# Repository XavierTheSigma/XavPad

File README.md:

# XavPad
XavPad is a 4x3 key macropad which uses KMK. I made this to help me be more productive.

## Features:
- 12 keys
- Simple case
- Dual layers 

## CAD Model:
The entire case fits together with 4 M3 screws.
The case has 2 seperate pieces: The Bottom and Sides, and the Top.

## PCB:
I made my PCB in KiCad

Schematic

PCB

## Firmware:
My hackpad uses [KMK](https://github.com/KMKfw/kmk_firmware) firmware.

- Swap between the 2 layers by double pressing the bottom left key
- The first layer are number pad 0-9
- The second layer are F1-12

For now it uses KMK but later on I might switch to QMK and add VIA support.

## BOM:
- 12x Cherry MX Switches
- 12x DSA Keycaps 
- 4x M3x16mm screws
- 12x through-hole 1N4148 Diodes
- 1x XIAO RP2040
- 1x Case (2 pieces)

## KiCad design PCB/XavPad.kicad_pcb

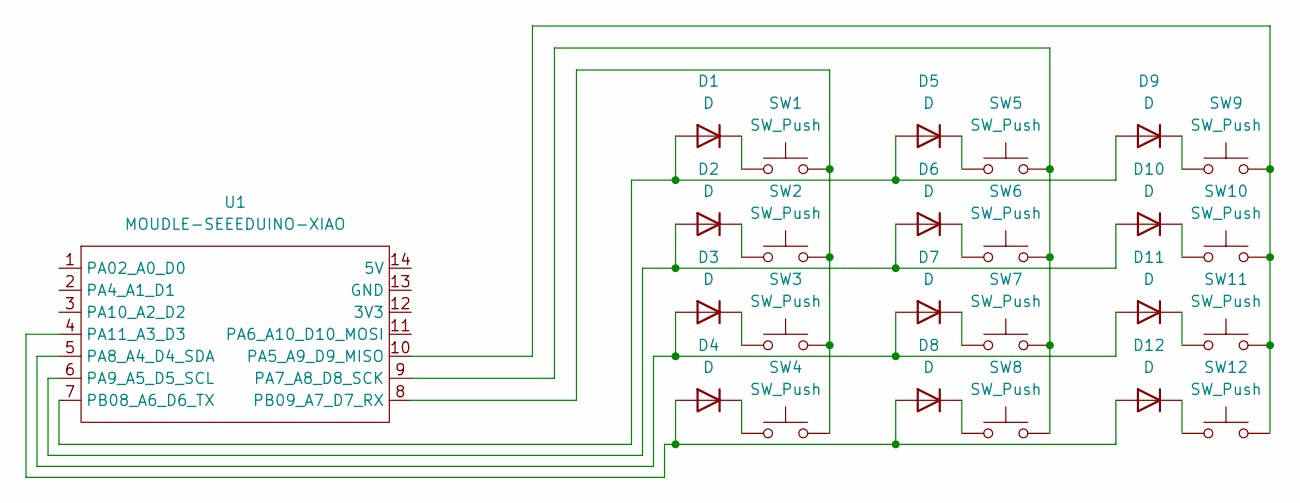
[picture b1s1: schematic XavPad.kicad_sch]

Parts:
D1, D2, D3, D4, D5, D6, D7, D8, D9, D10, D11, D12: D; D_DO-35_SOD27_P7.62mm_Horizontal
SW1, SW2, SW3, SW4, SW5, SW6, SW7, SW8, SW9, SW10, SW11, SW12: SW_Push; SW_Cherry_MX_1.00u_PCB
U1: MOUDLE-SEEEDUINO-XIAO; XIAO-Generic-Hybrid-14P-2.54-21X17.8MM

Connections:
unnamed: D1.2 (A), D5.2 (A), D9.2 (A), U1.7 (PB08_A6_D6_TX)
unnamed: D1.1 (K), SW1.1
unnamed: D2.1 (K), SW2.1
unnamed: D3.1 (K), SW3.1
unnamed: D4.1 (K), SW4.1
unnamed: D5.1 (K), SW5.1
unnamed: D6.1 (K), SW6.1
unnamed: D7.1 (K), SW7.1
unnamed: D8.1 (K), SW8.1
unnamed: D9.1 (K), SW9.1
unnamed: D2.2 (A), D6.2 (A), D10.2 (A), U1.6 (PA9_A5_D5_SCL)
unnamed: D10.1 (K), SW10.1
unnamed: D3.2 (A), D7.2 (A), D11.2 (A), U1.5 (PA8_A4_D4_SDA)
unnamed: D11.1 (K), SW11.1
unnamed: D4.2 (A), D8.2 (A), D12.2 (A), U1.4 (PA11_A3_D3)
unnamed: D12.1 (K), SW12.1
unnamed: SW9.2, SW10.2, SW11.2, SW12.2, U1.10 (PA5_A9_D9_MISO)
unnamed: SW5.2, SW6.2, SW7.2, SW8.2, U1.9 (PA7_A8_D8_SCK)
unnamed: SW1.2, SW2.2, SW3.2, SW4.2, U1.8 (PB09_A7_D7_RX)

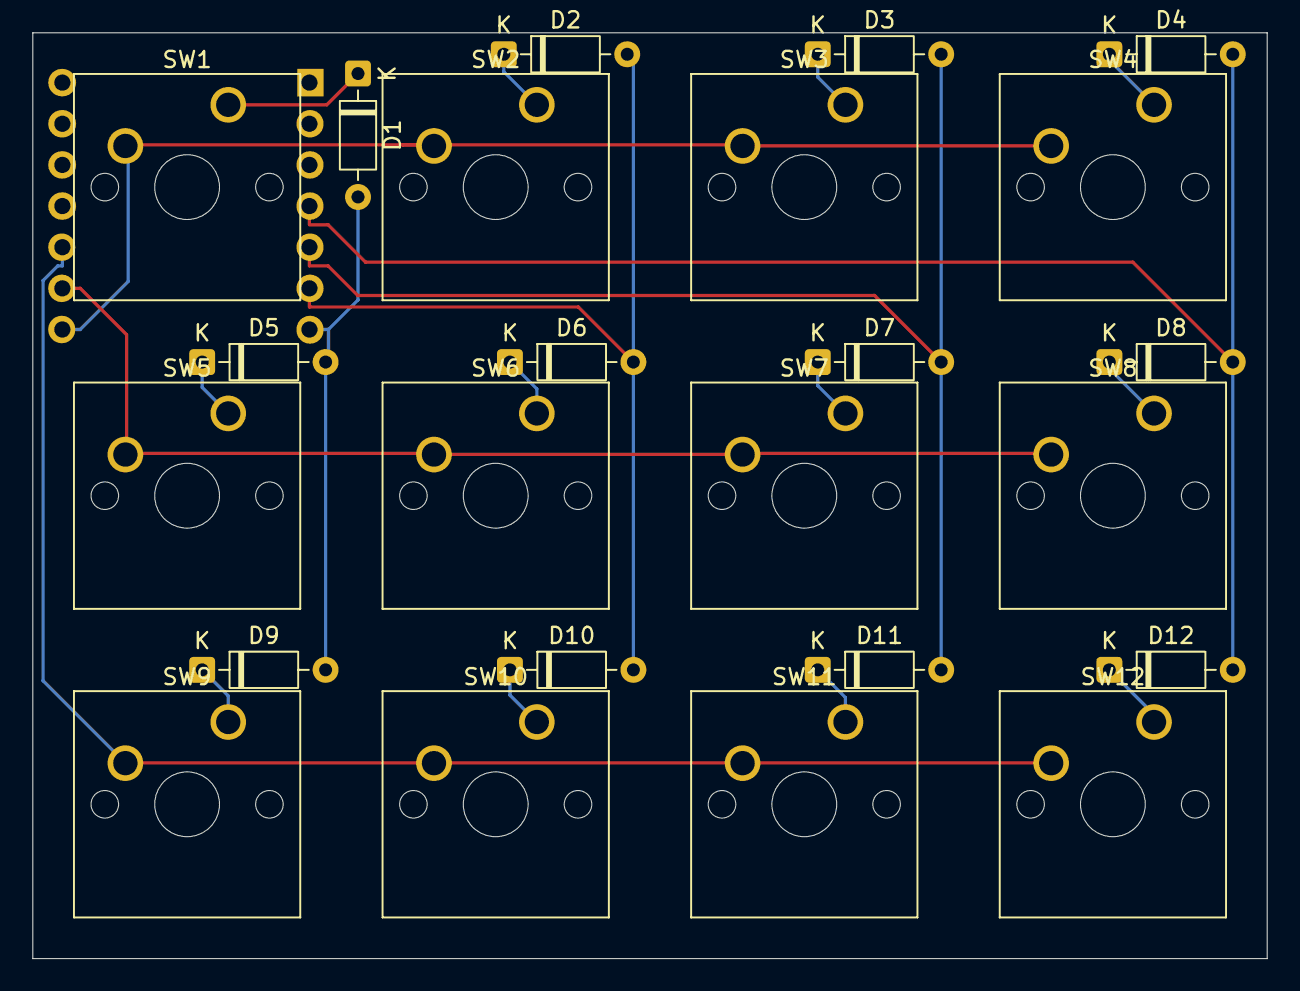
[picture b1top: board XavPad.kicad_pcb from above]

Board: 2 copper layers, 76.2 x 57.2 mm, 25 parts (1 on the bottom side), 19 nets.

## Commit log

2026-03-06 PCB + Firmware
2026-03-06 Added Case + added drill holes
2026-03-06 Renaming
2026-03-06 README
2026-03-06 Modified Shell
2026-03-06 Assets
2026-03-06 Adjusted Readme
2026-03-06 Read me touch ups
2026-03-09 Added space for the XIAO (3.5mm)
2026-03-09 Added BOM.csv
2026-03-09 Added Screw Indents
2026-03-09 Small Adjustment To BOM
